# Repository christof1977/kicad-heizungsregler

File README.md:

Heizungsteuerung

basierend auf Raspberry Pi Zero
- 10BaseT Ethernet (ENC28J60)
- Schmalspur PoE: 24V Eingang über die äusseren Päärchen
- Step-Down-Converter auf 5V
- MBus-Interface zum Auslesen von Wärmemengenzähler
- Anschluss für OneWire-Temperatursensor
- Anschluss für 8-Kanal-Relais-Karte
- Steckplatz für 0,96" Oled-Display
- I2C-Anschluss
- DS18B20
- Zwei Port für weitere OneWires

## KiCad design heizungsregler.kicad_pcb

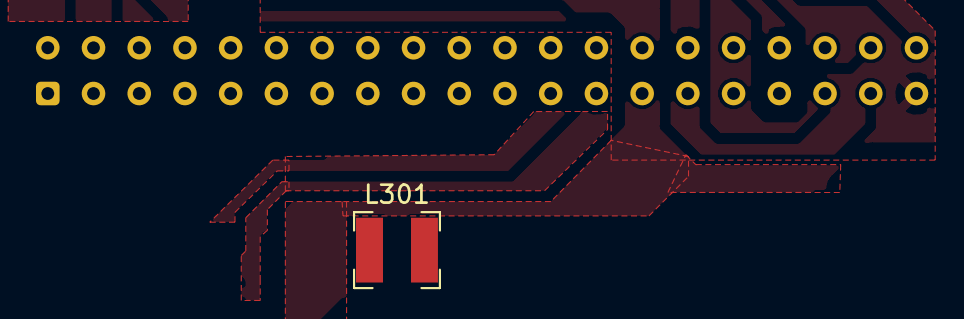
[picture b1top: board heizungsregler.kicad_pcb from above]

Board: 2 copper layers, 3 parts (1 on the bottom side), 2 nets, no tracks yet.

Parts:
J101: RPi_GPIO; Samtec_HLE-120-02-xx-DV-TE_2x20_P2.54mm_Horizontal
L301: 270U; L_Bourns-SRN4018
U101: oled_0.96

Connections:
+5V: J101.2, J101.4
GND: J101.6, J101.9, J101.14, J101.20, J101.25, J101.30, J101.34, J101.39

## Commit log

2018-12-05 Added pro-File, submodules
2018-12-05 added .gitignore
2018-12-05 Erstes Design auf Basis RPi_Zero_pHat: Ethernet fertig, PoE fertig
2018-12-05 Datenblätter und Schaltplan TPS54231 eingecheckt
2018-12-06 Mbus hinzugefügt
2018-12-06 Schaltplan weitergemacht, Footprints zugeordnet
2018-12-07 Platzierung begonnen, Signalnamen ENC korrigiert
2018-12-07 Backup-Datei aus git entfernt
2018-12-07 ENC28J60 platziert und geroutet
2018-12-07 Noch mehr Layout
2018-12-08 Relais geroutet
2018-12-09 Design weiter bearbeitet
2018-12-10 TPS54231 geroutet
2018-12-19 Transistoren für Relais eingefügt, Pull-Ups für I2C, zusätzlicher Spannungseingang, Layout fertig
2018-12-19 Readme angepasst
2018-12-21 Masseflächen zwischen Leitungen
2018-12-24 Änderungen nach Review, Layout fertig
2018-12-24 Footprint katualisiert, klitzekleine Aenderungen
2018-12-24 Fertigungsdaten erzeugt
2019-01-17 Bauteilwerte beim Bestücken angepasst
